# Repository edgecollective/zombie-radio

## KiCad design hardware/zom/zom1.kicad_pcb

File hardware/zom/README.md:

## 3.3V regulator:

4.75 - 36V input, 500 mA output: 

https://www.digikey.com/product-detail/en/cui-inc/VX7803-500/102-4243-ND/7350282

6V - 36V input, 1 A output:

https://www.digikey.com/products/en/power-supplies-board-mount/dc-dc-converters/922?k=vx78-&k=&pkeyword=vx7805&pv1120=203&FV=ffe0039a%2C17d4005e&quantity=0&ColumnSort=0&page=1&pageSize=25

## kicad refs
https://hackaday.io/project/13483-esp32-kicad-library
https://github.com/tomtor/STM32-RFM95-PCB

##

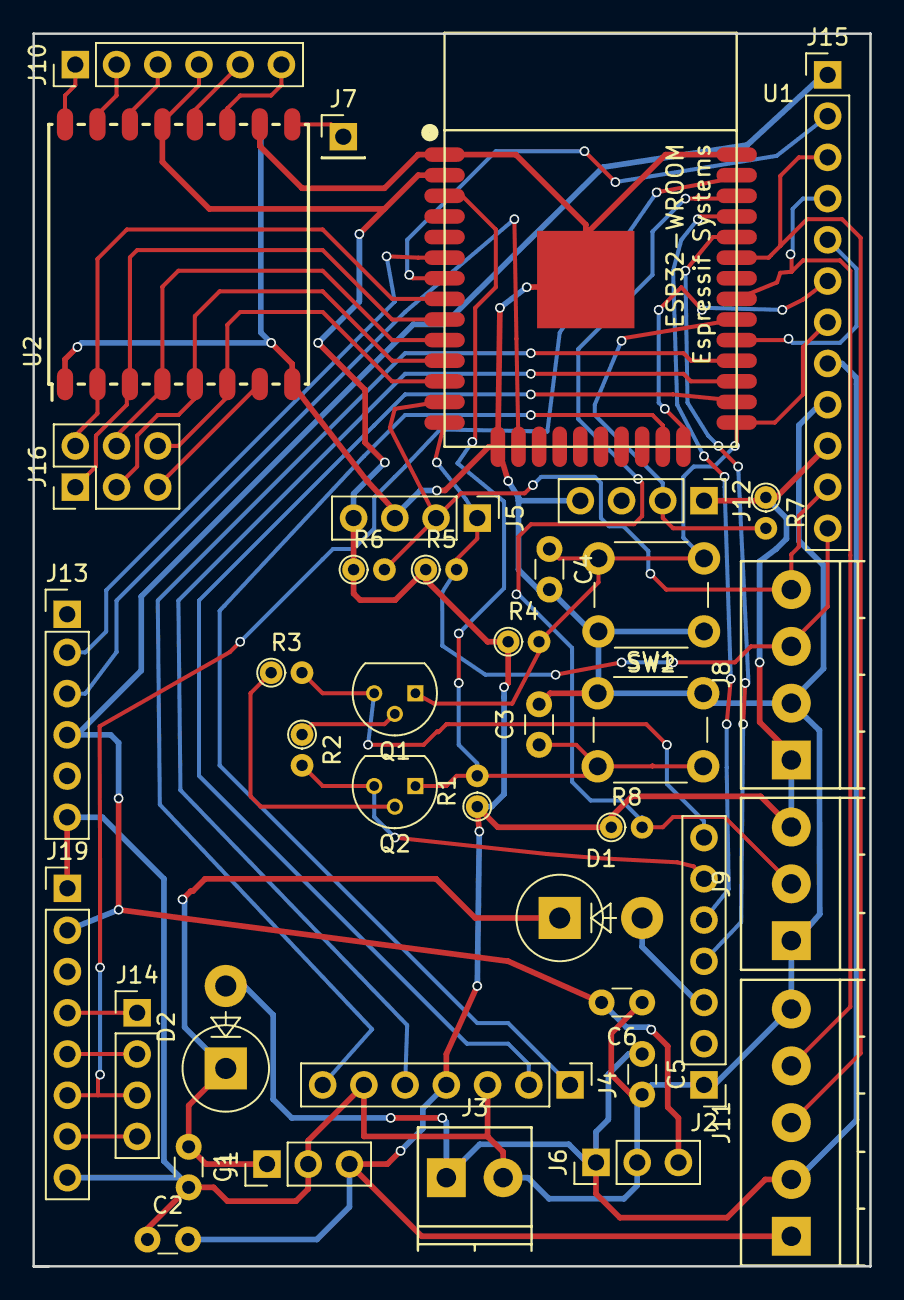
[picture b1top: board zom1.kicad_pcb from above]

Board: 2 copper layers, 51.6 x 75.9 mm, 39 parts (0 on the bottom side), 45 nets.

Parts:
C1, C5: 10 uF; C_Disc_D3.0mm_W1.6mm_P2.50mm
C2, C6: 22 uF; C_Disc_D3.0mm_W1.6mm_P2.50mm
C3, C4: C; C_Disc_D3.0mm_W1.6mm_P2.50mm
D1, D2: D; D_DO-201_P5.08mm_Vertical_AnodeUp
J1: REG:3V3; Socket_Strip_Straight_1x03_Pitch2.54mm
J2: prog; Pin_Header_Straight_1x07_Pitch2.54mm
J3: VINS; TerminalBlock_Phoenix_PT-3.5mm_2pol
J4: sdcard; Pin_Header_Straight_1x07_Pitch2.54mm
J5: i2c-a; Pin_Header_Straight_1x04_Pitch2.54mm
J6: REG:5V; Pin_Header_Straight_1x03_Pitch2.54mm
J7: ANT; Pin_Header_Straight_1x01_Pitch2.54mm
J8: i2c-c; TerminalBlock_Phoenix_PT-3.5mm_4pol
J9: 1wire; TerminalBlock_Phoenix_PT-3.5mm_3pol
J10: LBD; Pin_Header_Straight_1x06_Pitch2.54mm
J11: uart; TerminalBlock_Phoenix_PT-3.5mm_5pol
J12: dht22; Pin_Header_Straight_1x04_Pitch2.54mm
J13: 9602-a; Pin_Header_Straight_1x06_Pitch2.54mm
J14: satx; Pin_Header_Straight_1x04_Pitch2.54mm
J15: misc; Pin_Header_Straight_1x12_Pitch2.54mm
J16: LBO; Pin_Header_Straight_2x03_Pitch2.54mm
J19: 9602-b; Pin_Header_Straight_1x08_Pitch2.54mm
Q1, Q2: Q_NPN_CBE; TO-92_Molded_Narrow
R1, R4: 10K; R_Axial_DIN0204_L3.6mm_D1.6mm_P1.90mm_Vertical
R2, R3, R5, R6, R7, R8: R; R_Axial_DIN0204_L3.6mm_D1.6mm_P1.90mm_Vertical
SW1, SW2: SW_Push; SW_PUSH_6mm
U1: ESP32-WROOM
U2: RFM95HW; RFM95

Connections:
0: C4.1, J15.7, Q1.1, R4.2, SW2.2, U1.25
2: J15.6, U1.24
4: J4.2, U1.26
5: J15.5, U1.29
12/SDA: J5.1, J8.3, J15.12, R5.2, U1.14
13: J13.3, U1.16
14/SCL: J5.2, J8.4, J15.11, R6.2, U1.13
15: J4.1, U1.23
16: J4.5, U1.27
17: J4.7, U1.28
18: J12.2, R7.2, U1.30
19: J11.4, J15.4, U1.31
21: J11.3, J15.3, U1.33
22: J9.2, R8.2, U1.36
23/SAT_SLEEP: J14.3, J19.6, U1.37
25: J16.4, U1.10, U2.4
26: J16.3, U1.11, U2.5
27: J16.6, U1.12, U2.6
32: J16.2, U1.8, U2.2
33: J16.1, U1.9, U2.3
34: J13.2, U1.6
35: J15.2, U1.7
+3V3: C2.2, J1.3, J4.4, J5.4, J8.1, J9.3, J10.4, J11.1, J12.1, J15.10, R1.1, R4.1, R5.1, R6.1, R7.1, R8.1, U1.2, U2.13
+5V: C6.2, J6.3, J13.4, J15.1, J19.2
DIO0: J10.3, U2.14
DIO1: J10.2, U2.15
DIO2: J10.1, U2.16
DIO3: J10.6, U2.11
DIO4: J10.5, U2.12
DIO5: J16.5, U2.7
DTR: J2.7, Q1.3, R3.2
GND: C1.2, C2.1, C3.2, C4.2, C5.2, C6.1, J1.2, J2.1, J3.2, J4.3, J4.6, J5.3, J6.2, J8.2, J9.1, J11.5, J12.4, J13.6, J15.9, J19.1, J19.8, SW1.1, SW2.1, U1.1, U1.15, U1.38, U1.39, U2.1, U2.8, U2.10
unnamed: C1.1, D1.1, D2.1, J1.1
unnamed: J7.1, U2.9
unnamed: Q1.2, R2.1
unnamed: Q2.2, R3.1
RESET: C3.1, Q2.1, R1.2, SW1.2, U1.3
RTS: J2.6, Q2.3, R2.2
RX0: J2.4, U1.34
SAT_LION: J14.4, J19.7
SAT_NETWORK_AVAIL: J14.2, J19.5
SAT_RING_INDICATOR: J14.1, J19.4
TX0: J2.5, U1.35
VBUS: D1.2, J2.3
VIN: C5.1, D2.2, J3.1, J6.1, J11.2, J15.8

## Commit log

2018-09-01 Update README.md
    spruced up markdown
2018-09-01 Update README.md
    fixed file name discrepancy
2018-09-01 Update README.md
    added missing module put
2018-09-06 some doc
2018-09-11 added doc and setup functionality
2018-09-11 load network settings from secret_settings.py; print IP address on start up; changed pin settings
2018-09-11 update docs
2018-09-11 tagged all async coro defs
2018-09-12 refactored code; extracted local settings; NOT TESTED yet
2018-09-12 setup instruction a little more complete
2018-09-12 automate upip dependencies install
2018-09-12 yet more files needed for completeness
2018-09-12 name change for local settings
2018-09-12 working at least up to import upip_install_deps step
2018-09-12 working for CWV settings
2018-09-12 restored DWB settings EXCEPT use_oled_display == False
2018-09-12 fixed fornatting
2018-09-12 now we check for successful install, then delete this script since it is no longer neeeded
2018-09-13 class for wrapped circular queue backed by file
